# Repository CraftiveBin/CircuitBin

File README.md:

## ESP8266 12E
**single Layer Breakout Board**

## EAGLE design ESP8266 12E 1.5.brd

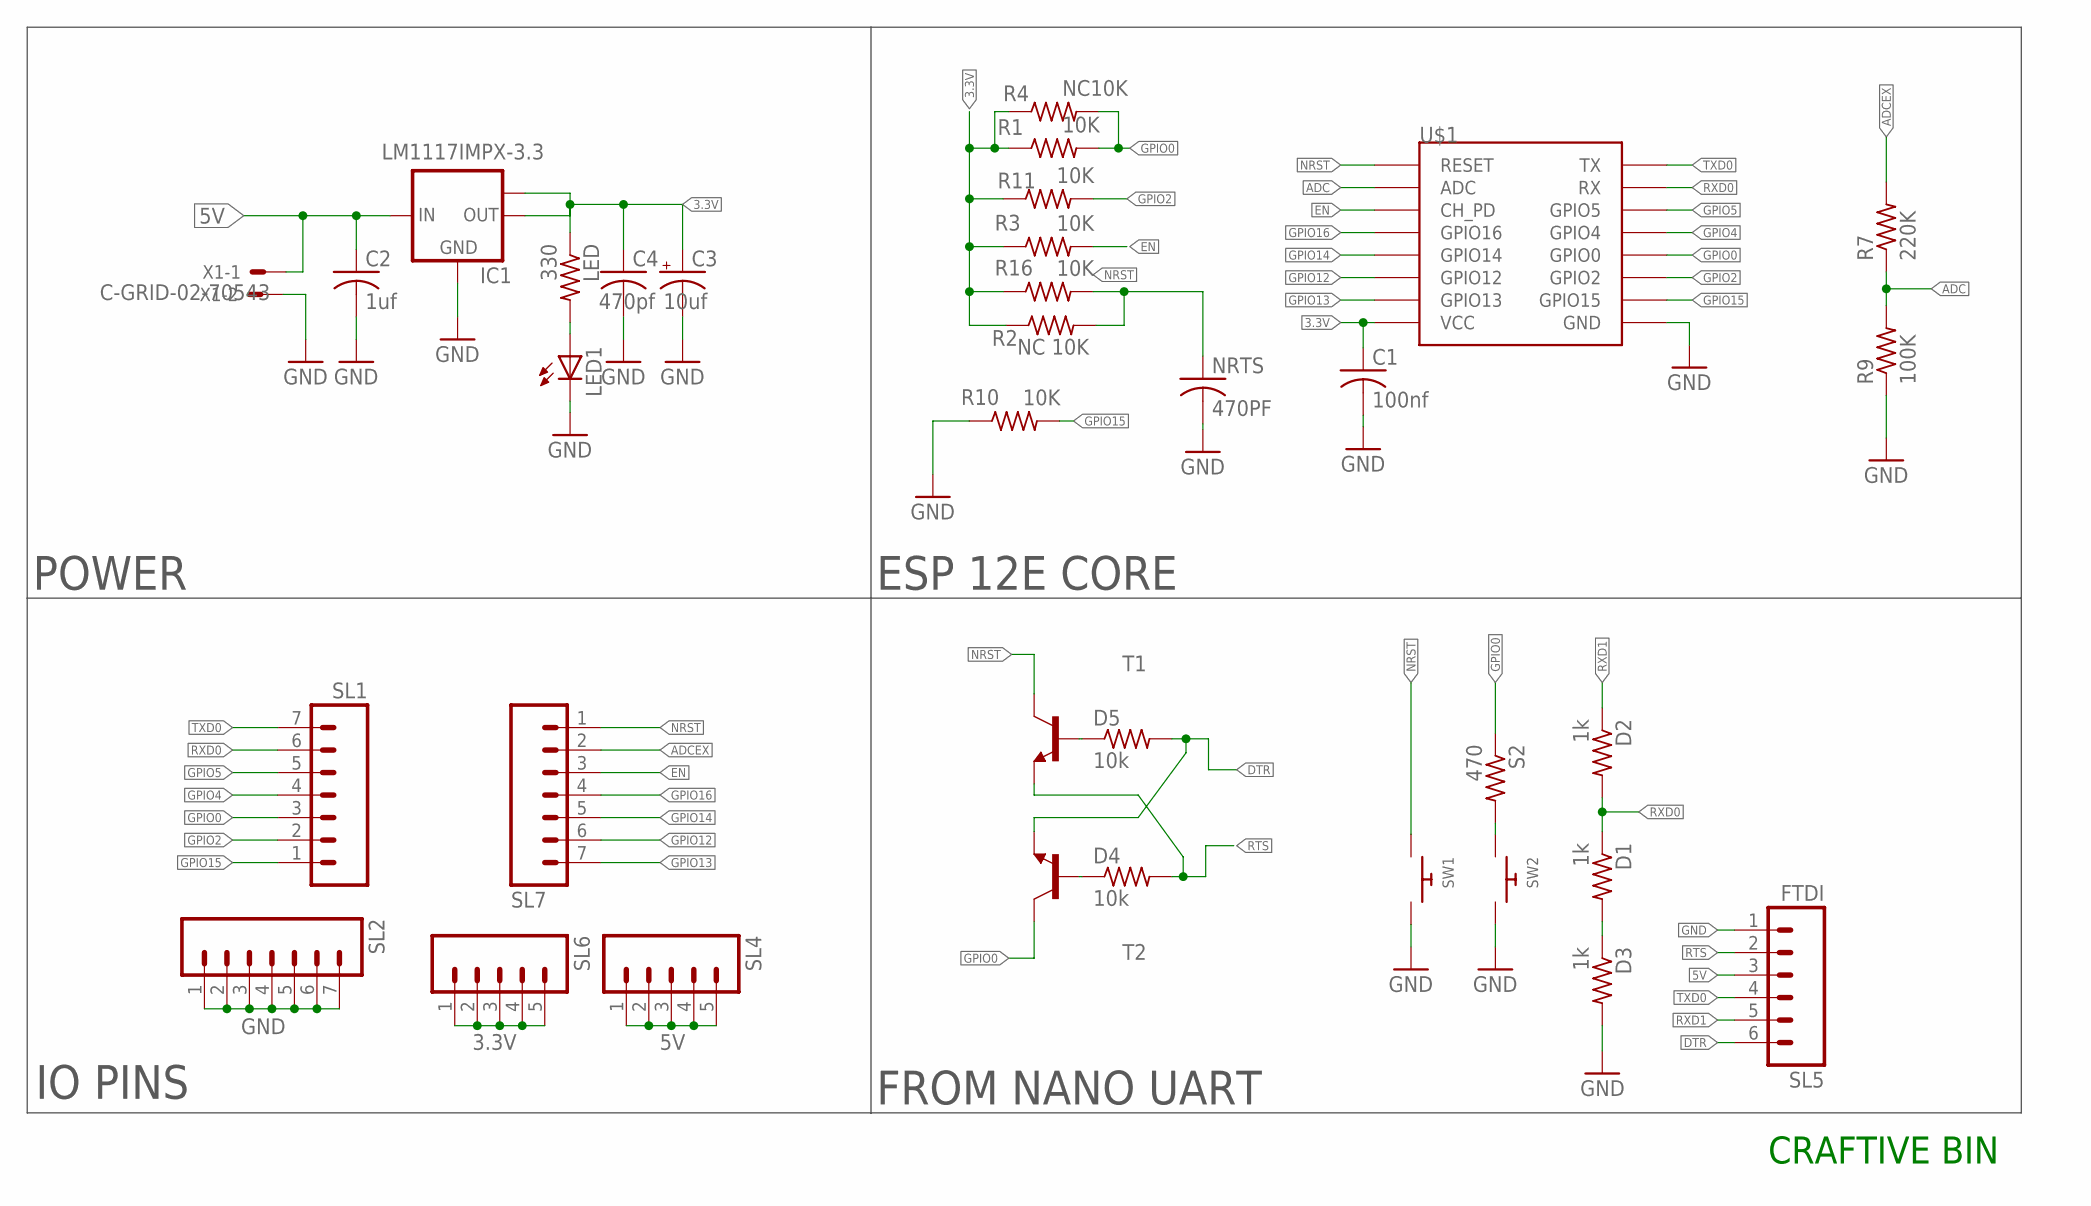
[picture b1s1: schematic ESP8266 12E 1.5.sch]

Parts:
C1: 100nf; C050-025X075
C2: 1uf; C050-030X075
C3: 10uf; E2,5-5
C4: 470pf; C050-025X075
D1, D2, D3: 1k; 0309/10
D4, D5: 10k; 0309/10
IC1: LM1117IMPX-3.3; SOT223
LED: 330; 0309/10
LED1: LED3MM
NRTS: 470PF; C050-025X075
R1, R3, R10, R11, R16: 10K; 0207/7
R2: NC 10K; M1206
R4: NC10K; 0207/7
R7: 220K; 0309/10
R9: 100K; 0309/10
S2: 470; 0309/10
SL1, SL2, SL7: M07; 07P
SL4, SL6: M05; 05P
SL5: FTDI; 06P
SW1, SW2: SWITCH_PUSHBUTTONEVQ; 0204/5
T1, T2: 2N2222; TO92-EBC-OVAL
U$1: ESP8266; ESP8266MIRROR
X1: C-GRID-02-70543; 70543-02

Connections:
3.3V: C1.1, C3.+, C4.1, IC1.2 (OUT), IC1.TAB (OUT1), LED.1, R1.1, R2.1, R3.1, R4.1, R11.1, R16.1, SL6.1, SL6.2, SL6.3, SL6.4, SL6.5, U$1.VCC
5V: C2.1, IC1.3 (IN), SL4.1, SL4.2, SL4.3, SL4.4, SL4.5, SL5.3, X1.1
ADC: R7.1, R9.2, U$1.ADC
ADCEX: R7.2, SL7.2
DTR: D5.2, SL5.6, T2.E
EN: R3.2, SL7.3, U$1.EN (CH_PD)
GND: C1.2, C2.2, C3.-, C4.2, D3.2, IC1.1 (GND), LED1.K (C), NRTS.2, R9.1, R10.1, SL2.1, SL2.2, SL2.3, SL2.4, SL2.5, SL2.6, SL2.7, SL5.1, SW1.2, SW2.2, U$1.GND, X1.2
GPIO0: R1.2, R4.2, S2.1, SL1.3, T2.C, U$1.0 (GPIO0)
GPIO2: R11.2, SL1.2, U$1.2 (GPIO2)
GPIO4: SL1.4, U$1.4 (GPIO4)
GPIO5: SL1.5, U$1.5 (GPIO5)
GPIO12: SL7.6, U$1.12 (GPIO12)
GPIO13: SL7.7, U$1.13 (GPIO13)
GPIO14: SL7.5, U$1.14 (GPIO14)
GPIO15: R10.2, SL1.1, U$1.15 (GPIO15)
GPIO16: SL7.4, U$1.16 (GPIO16)
unnamed: D5.1, T1.B
unnamed: D4.1, T2.B
unnamed: S2.2, SW2.1
unnamed: LED.2, LED1.A
unnamed: D1.2, D3.1
NRST: NRTS.1, R2.2, R16.2, SL7.1, SW1.1, T1.C, U$1.RST (RESET)
RTS: D4.2, SL5.2, T1.E
RXD0: D1.1, D2.2, SL1.6, U$1.RX
RXD1: D2.1, SL5.5
TXD0: SL1.7, SL5.4, U$1.TX

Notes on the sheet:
ESP 12E CORE
FROM NANO UART
POWER
IO PINS
CRAFTIVE BIN

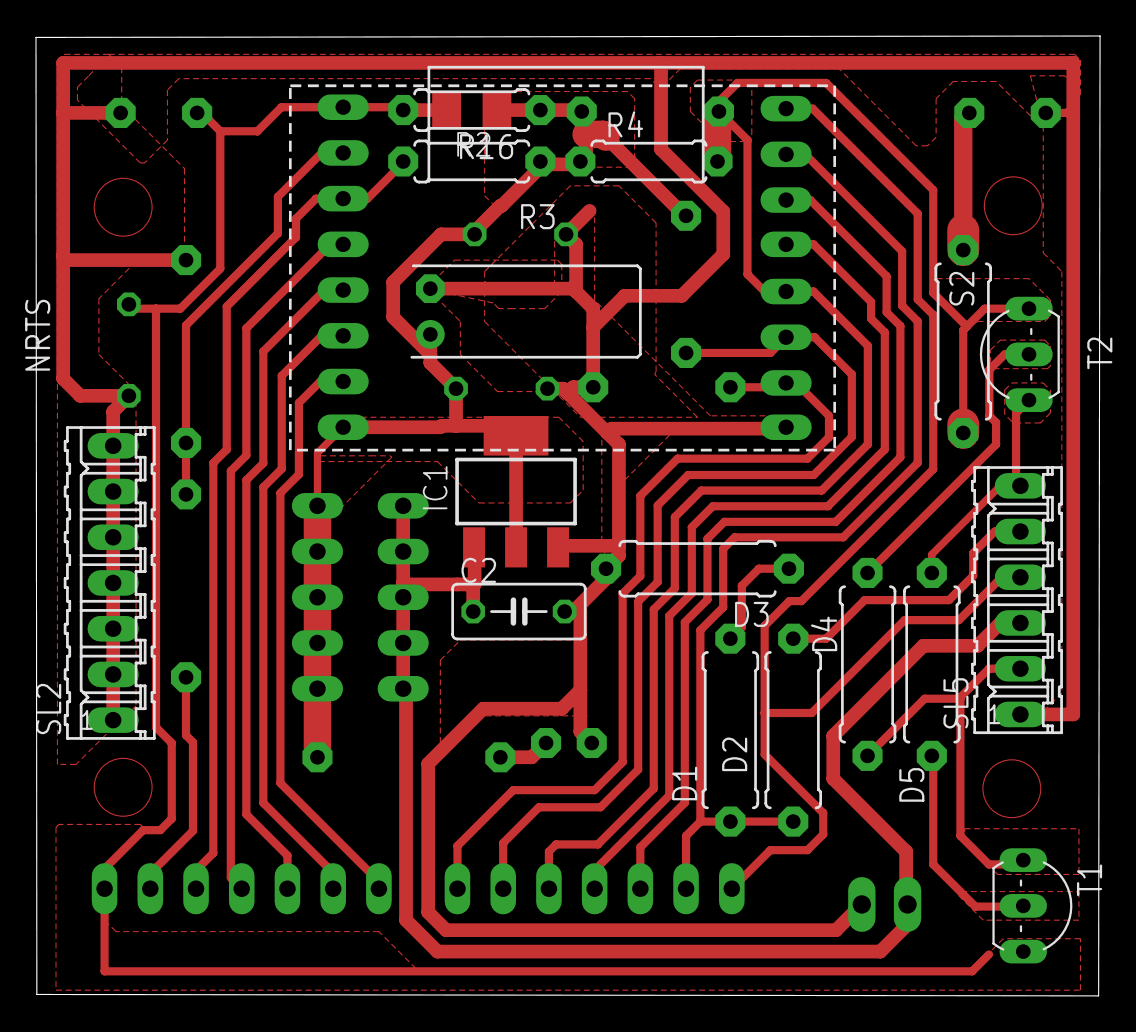
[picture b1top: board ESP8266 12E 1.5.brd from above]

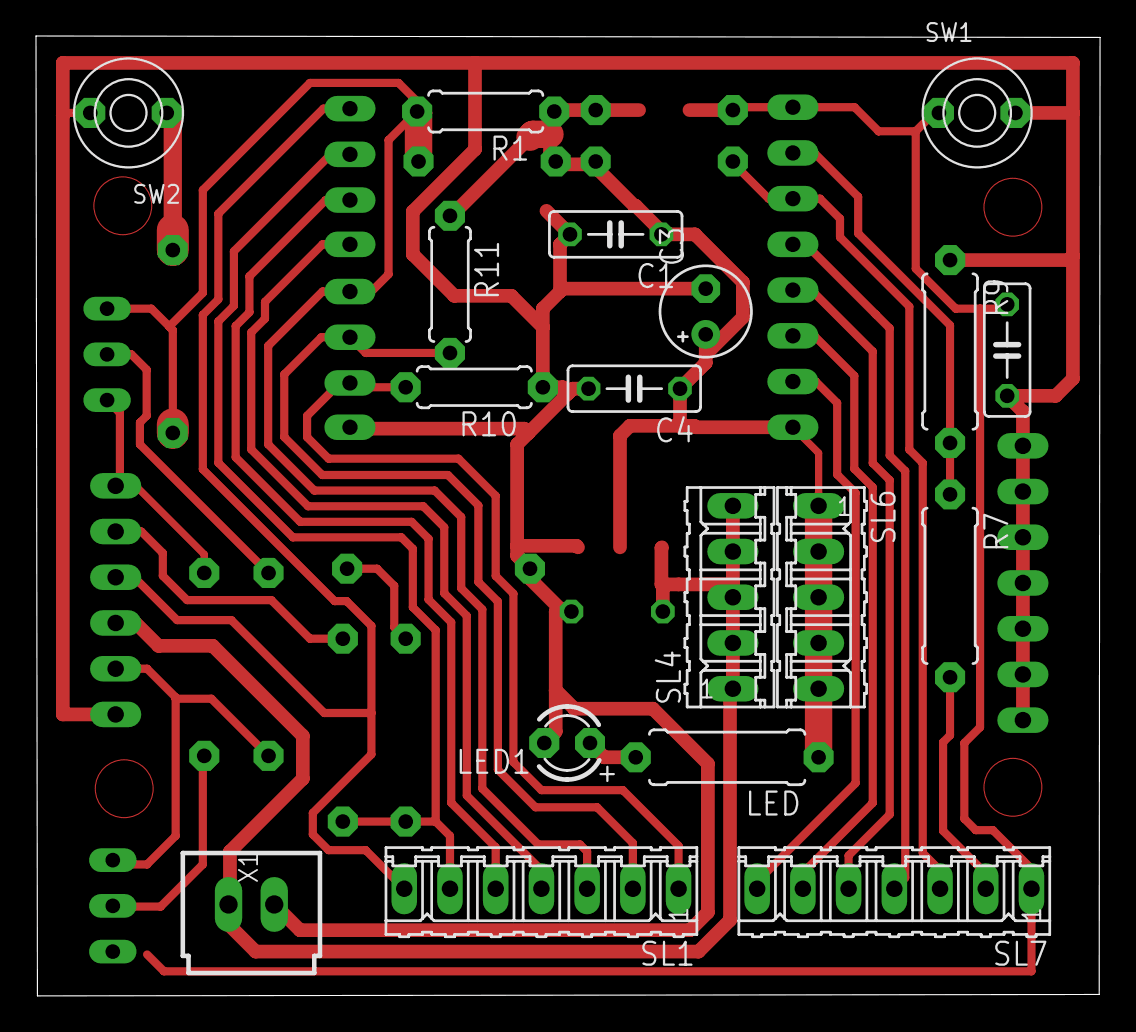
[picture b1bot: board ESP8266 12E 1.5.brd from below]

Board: 2 copper layers, 59.1 x 53.3 mm, 35 parts (18 on the bottom side), 26 nets.

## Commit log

2020-12-13 Set theme jekyll-theme-slate
